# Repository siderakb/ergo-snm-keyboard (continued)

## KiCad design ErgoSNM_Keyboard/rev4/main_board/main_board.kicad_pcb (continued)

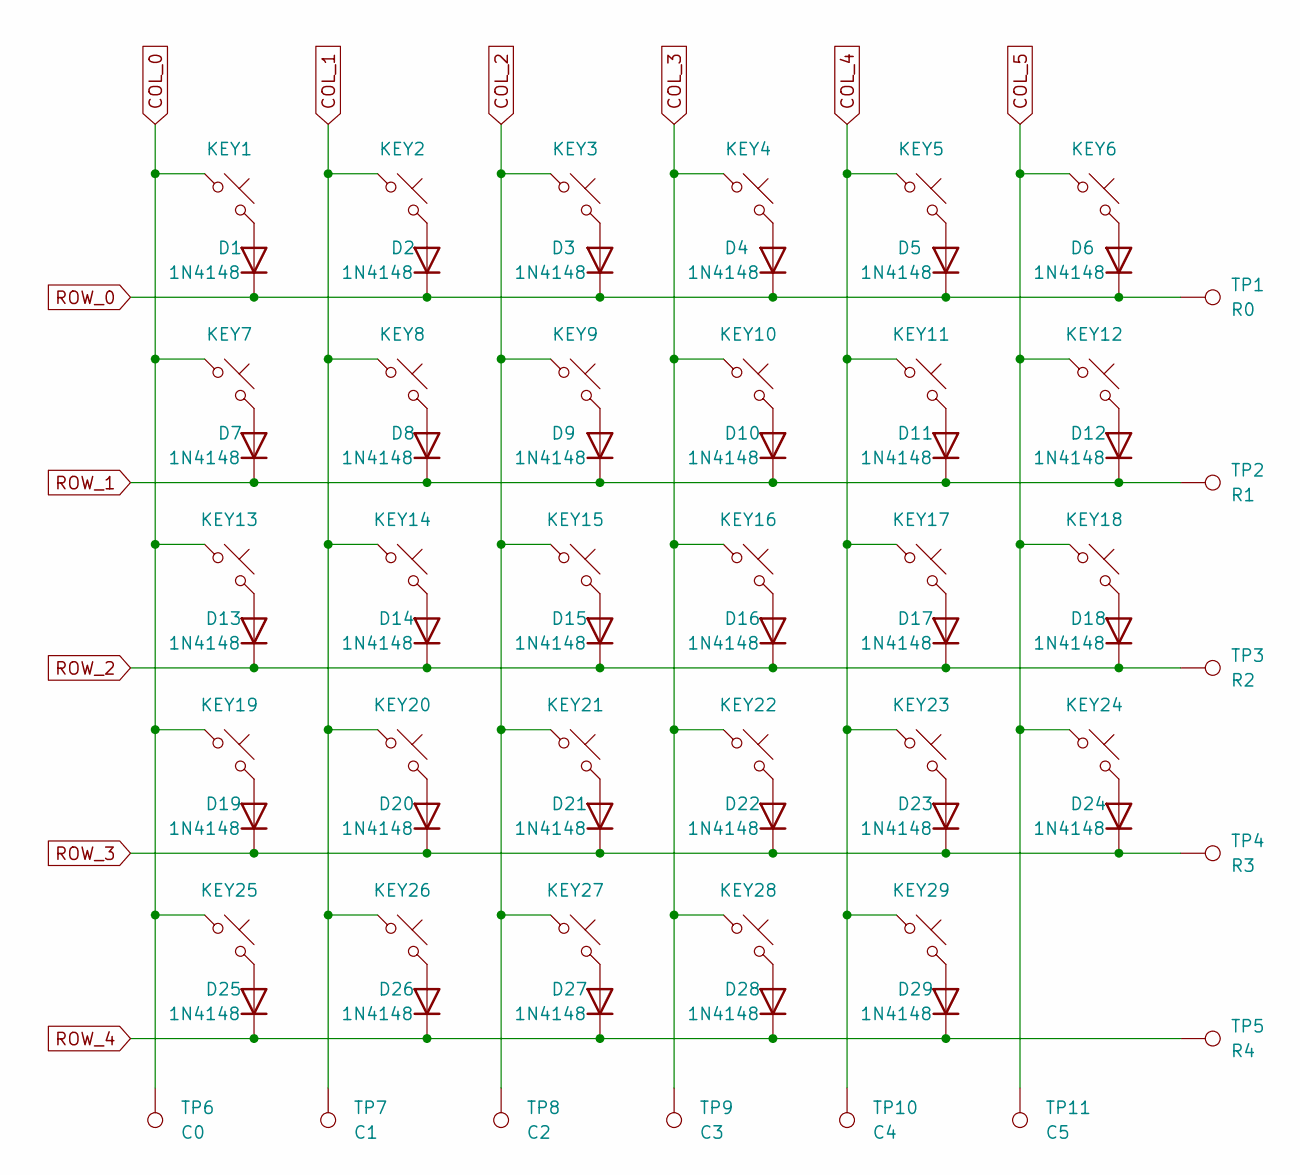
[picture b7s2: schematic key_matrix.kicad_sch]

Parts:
D1, D2, D3, D4, D5, D6, D7, D8, D9, D10, D11, D12, D13, D14, D15, D16, D17, D18, D19, D20, D21, D22, D23, D24, D25, D26, D27, D28, D29: 1N4148; D_SOD-123; MFR. Part # 1N4148W; JLCPCB Part # C81598
KEY1, KEY2, KEY3, KEY4, KEY5, KEY6, KEY7, KEY8, KEY9, KEY10, KEY11, KEY12, KEY13, KEY14, KEY15, KEY16, KEY17, KEY18, KEY19, KEY20, KEY21, KEY22, KEY23, KEY24, KEY25, KEY26, KEY27, KEY28, KEY29: SW_Push_45deg; SW_MX_Kailh_Choc_V1V2_HotSwap_Hybrid_double; MFR. Part # --
TP1: R0; TestPoint_Pad_D1.5mm; MFR. Part # --
TP2: R1; TestPoint_Pad_D1.5mm; MFR. Part # --
TP3: R2; TestPoint_Pad_D1.5mm; MFR. Part # --
TP4: R3; TestPoint_Pad_D1.5mm; MFR. Part # --
TP5: R4; TestPoint_Pad_D1.5mm; MFR. Part # --
TP6: C0; TestPoint_Pad_D1.5mm; MFR. Part # --
TP7: C1; TestPoint_Pad_D1.5mm; MFR. Part # --
TP8: C2; TestPoint_Pad_D1.5mm; MFR. Part # --
TP9: C3; TestPoint_Pad_D1.5mm; MFR. Part # --
TP10: C4; TestPoint_Pad_D1.5mm; MFR. Part # --
TP11: C5; TestPoint_Pad_D1.5mm; MFR. Part # --

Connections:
COL_0: KEY1.1, KEY7.1, KEY13.1, KEY19.1, KEY25.1, TP6.1; also elsewhere on the board
COL_1: KEY2.1, KEY8.1, KEY14.1, KEY20.1, KEY26.1, TP7.1; also elsewhere on the board
COL_2: KEY3.1, KEY9.1, KEY15.1, KEY21.1, KEY27.1, TP8.1; also elsewhere on the board
COL_3: KEY4.1, KEY10.1, KEY16.1, KEY22.1, KEY28.1, TP9.1; also elsewhere on the board
COL_4: KEY5.1, KEY11.1, KEY17.1, KEY23.1, KEY29.1, TP10.1; also elsewhere on the board
COL_5: KEY6.1, KEY12.1, KEY18.1, KEY24.1, TP11.1; also elsewhere on the board
unnamed: D1.2 (A), KEY1.2
unnamed: D2.2 (A), KEY2.2
unnamed: D3.2 (A), KEY3.2
unnamed: D4.2 (A), KEY4.2
unnamed: D5.2 (A), KEY5.2
unnamed: D6.2 (A), KEY6.2
unnamed: D7.2 (A), KEY7.2
unnamed: D8.2 (A), KEY8.2
unnamed: D9.2 (A), KEY9.2
unnamed: D10.2 (A), KEY10.2
unnamed: D11.2 (A), KEY11.2
unnamed: D12.2 (A), KEY12.2
unnamed: D13.2 (A), KEY13.2
unnamed: D14.2 (A), KEY14.2
unnamed: D15.2 (A), KEY15.2
unnamed: D16.2 (A), KEY16.2
unnamed: D17.2 (A), KEY17.2
unnamed: D18.2 (A), KEY18.2
unnamed: D19.2 (A), KEY19.2
unnamed: D20.2 (A), KEY20.2
unnamed: D21.2 (A), KEY21.2
unnamed: D22.2 (A), KEY22.2
unnamed: D23.2 (A), KEY23.2
unnamed: D24.2 (A), KEY24.2
unnamed: D25.2 (A), KEY25.2
unnamed: D26.2 (A), KEY26.2
unnamed: D27.2 (A), KEY27.2
unnamed: D28.2 (A), KEY28.2
unnamed: D29.2 (A), KEY29.2
ROW_0: D1.1 (K), D2.1 (K), D3.1 (K), D4.1 (K), D5.1 (K), D6.1 (K), TP1.1; also elsewhere on the board
ROW_1: D7.1 (K), D8.1 (K), D9.1 (K), D10.1 (K), D11.1 (K), D12.1 (K), TP2.1; also elsewhere on the board
ROW_2: D13.1 (K), D14.1 (K), D15.1 (K), D16.1 (K), D17.1 (K), D18.1 (K), TP3.1; also elsewhere on the board
ROW_3: D19.1 (K), D20.1 (K), D21.1 (K), D22.1 (K), D23.1 (K), D24.1 (K), TP4.1; also elsewhere on the board
ROW_4: D25.1 (K), D26.1 (K), D27.1 (K), D28.1 (K), D29.1 (K), TP5.1; also elsewhere on the board

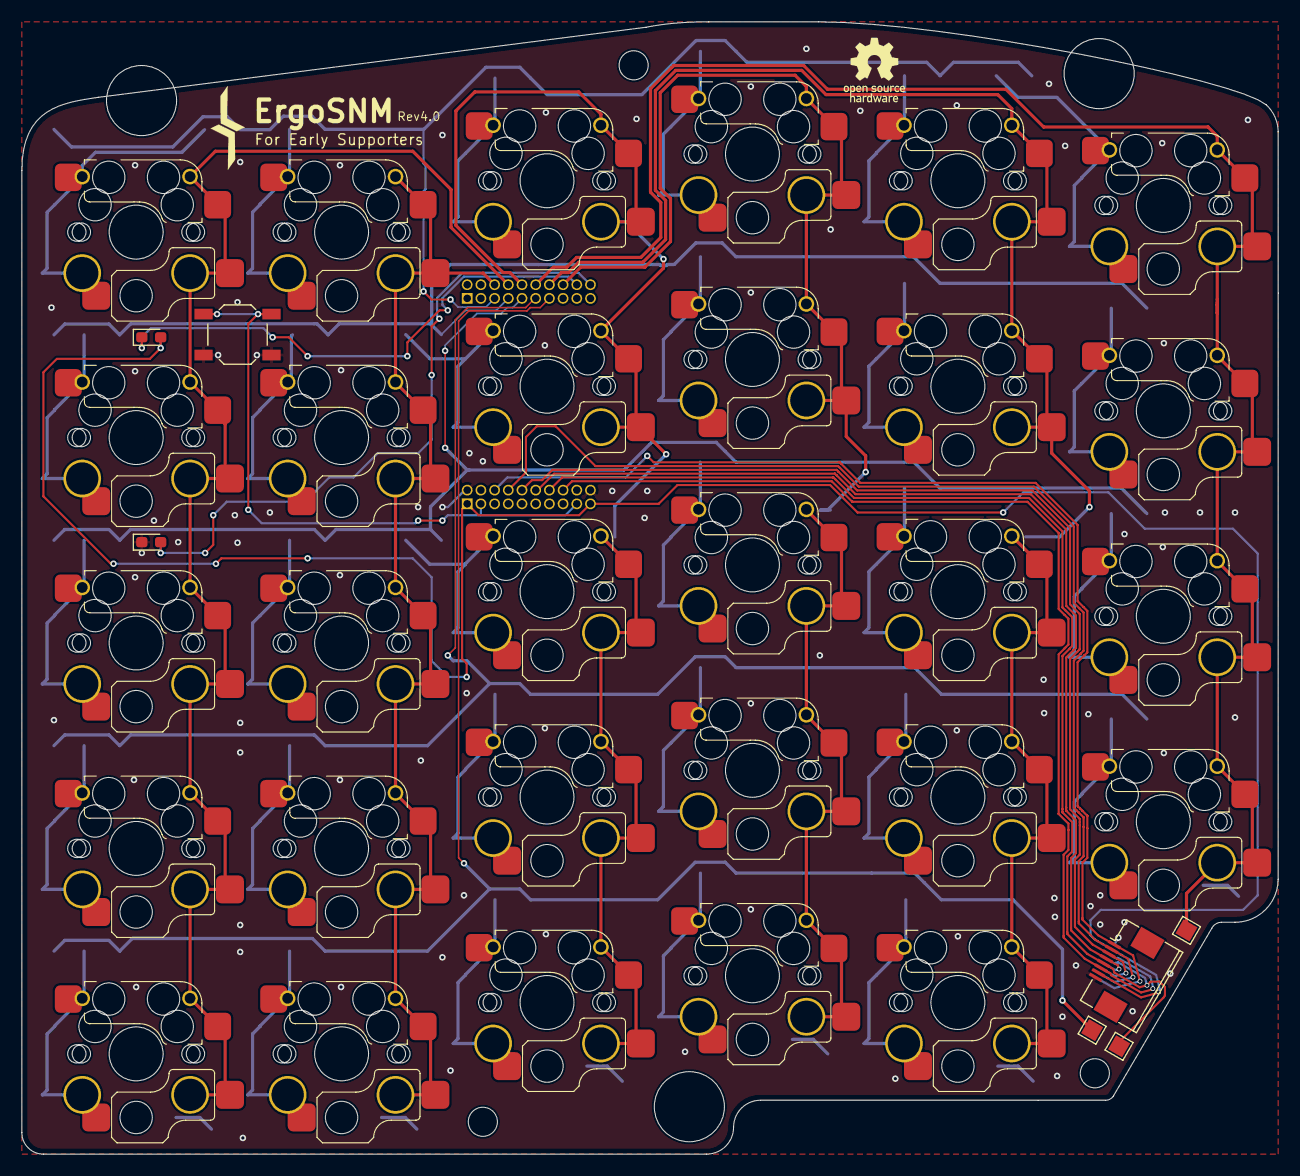
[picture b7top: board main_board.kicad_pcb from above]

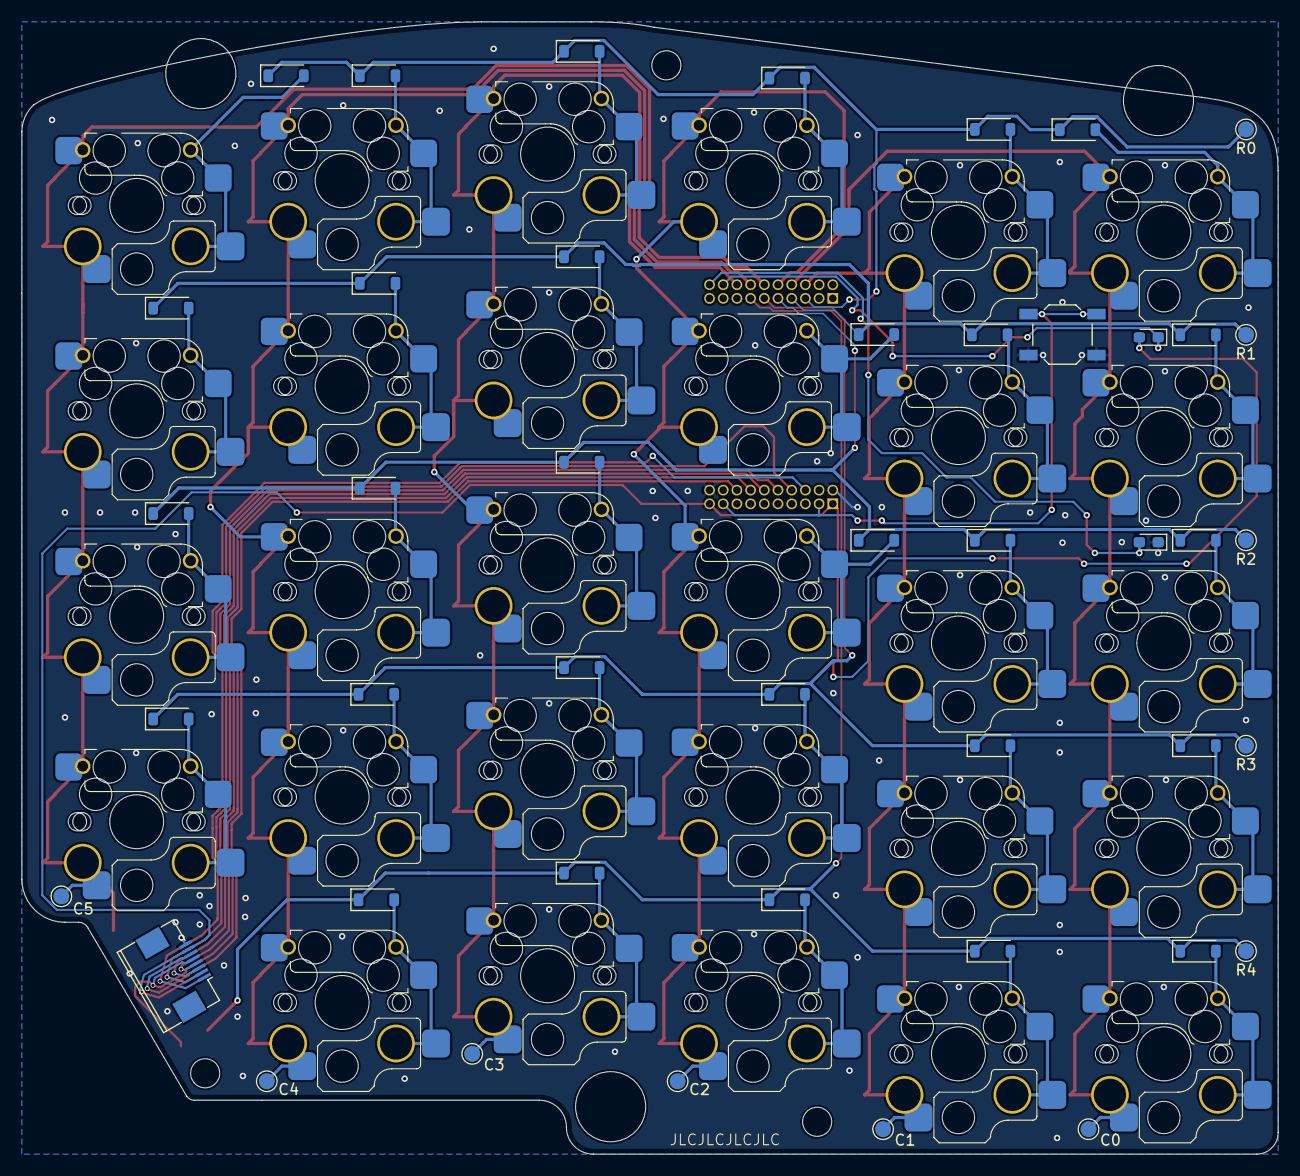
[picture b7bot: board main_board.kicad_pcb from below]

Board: 2 copper layers, 116.5 x 105.0 mm, 88 parts (48 on the bottom side), 51 nets.
